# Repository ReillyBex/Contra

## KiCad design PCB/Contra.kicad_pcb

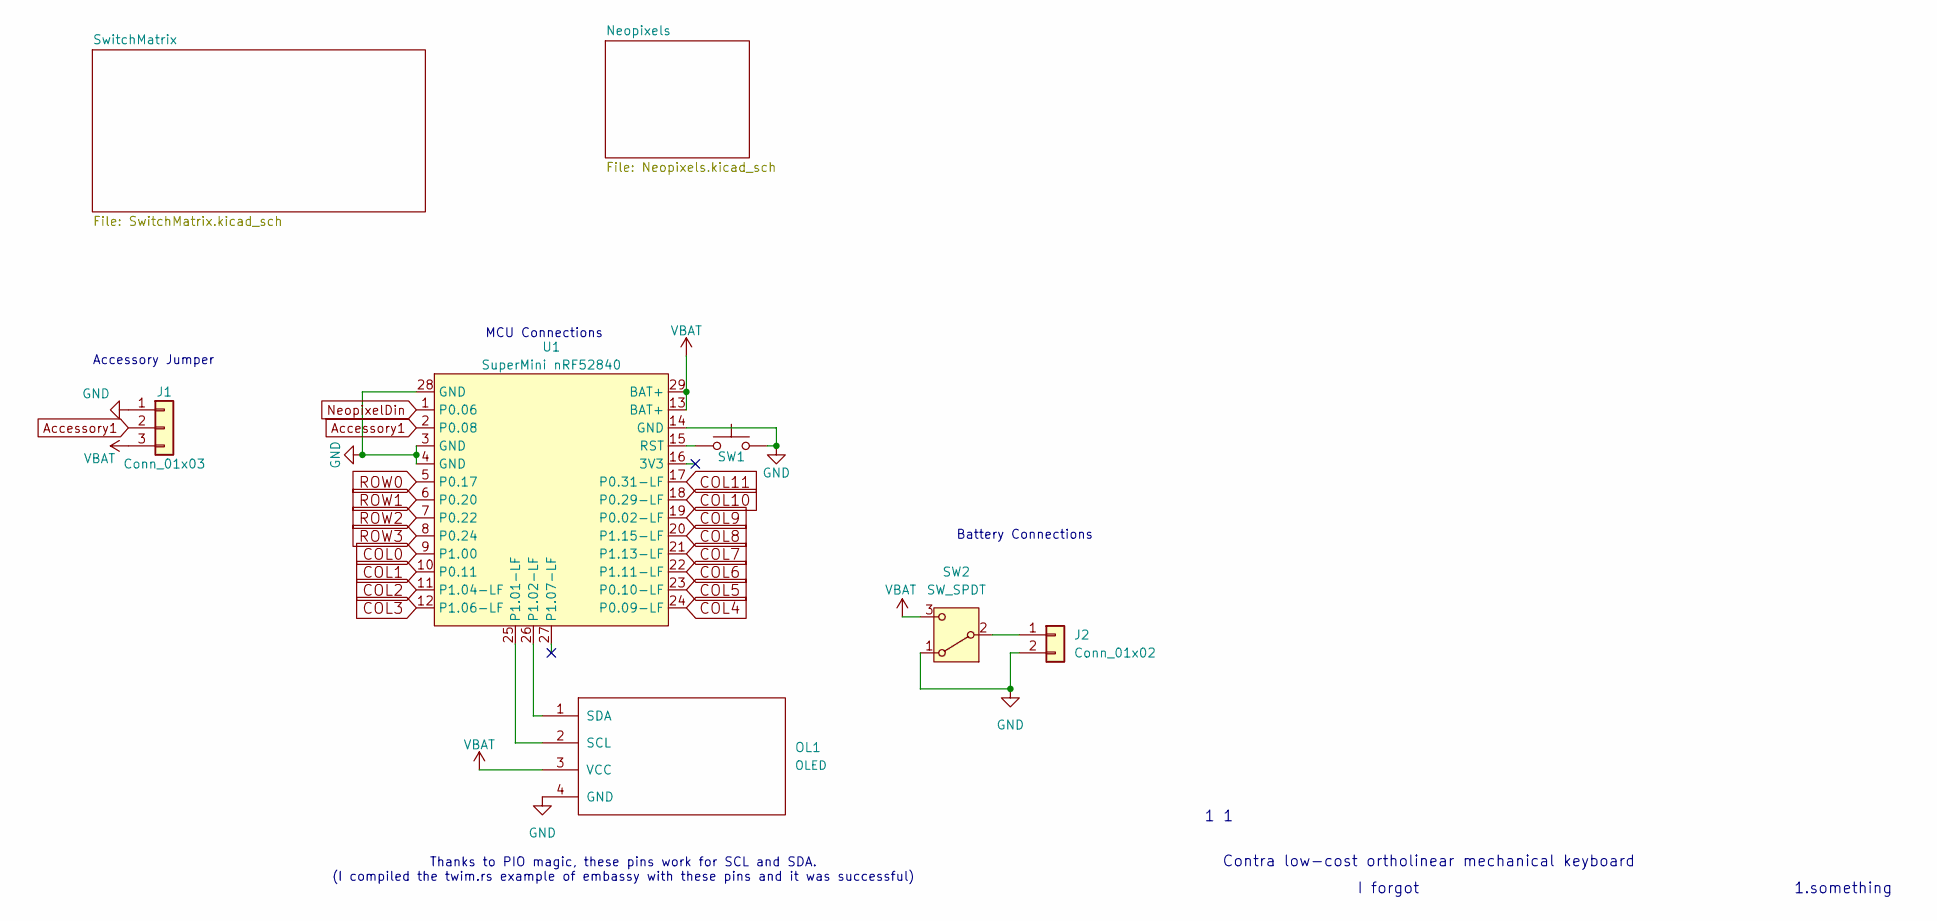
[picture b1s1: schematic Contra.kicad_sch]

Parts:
J1: Conn_01x03; PinHeader_1x03_P2.54mm_Horizontal
J2: Conn_01x02; JST_XH_S2B-XH-A_1x02_P2.50mm_Horizontal
OL1: OLED
SW1: SW_PUSH; SW_PUSH_1P1T_6x3.5mm_H5.0_APEM_MJTP1250
SW2: SW_SPDT; SW_Slide_SPDT_Angled_CK_OS102011MA1Q
U1: SuperMini nRF52840; SuperMini NRF52840

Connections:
Accessory1: J1.2, U1.2 (P0.08)
COL0: U1.9 (P1.00); also elsewhere on the board
COL1: U1.10 (P0.11); also elsewhere on the board
COL2: U1.11 (P1.04-LF); also elsewhere on the board
COL3: U1.12 (P1.06-LF); also elsewhere on the board
COL4: U1.24 (P0.09-LF); also elsewhere on the board
COL5: U1.23 (P0.10-LF); also elsewhere on the board
COL6: U1.22 (P1.11-LF); also elsewhere on the board
COL7: U1.21 (P1.13-LF); also elsewhere on the board
COL8: U1.20 (P1.15-LF); also elsewhere on the board
COL9: U1.19 (P0.02-LF); also elsewhere on the board
COL10: U1.18 (P0.29-LF); also elsewhere on the board
COL11: U1.17 (P0.31-LF); also elsewhere on the board
GND: J1.1, J2.2, OL1.4 (GND), SW1.2, SW2.1 (A), U1.3 (GND), U1.4 (GND), U1.14 (GND), U1.28 (GND); also elsewhere on the board
NeopixelDin: U1.1 (P0.06); also elsewhere on the board
unnamed: J2.1, SW2.2 (B)
unnamed: OL1.2 (SCL), U1.25 (P1.01-LF)
unnamed: OL1.1 (SDA), U1.26 (P1.02-LF)
unnamed: SW1.1, U1.15 (RST)
ROW0: U1.5 (P0.17); also elsewhere on the board
ROW1: U1.6 (P0.20); also elsewhere on the board
ROW2: U1.7 (P0.22); also elsewhere on the board
ROW3: U1.8 (P0.24); also elsewhere on the board
VBAT: J1.3, OL1.3 (VCC), SW2.3 (C), U1.13 (BAT+), U1.29 (BAT+); also elsewhere on the board

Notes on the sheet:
1.something
Battery Connections
1 1
I forgot
MCU Connections
Thanks to PIO magic, these pins work for SCL and SDA. (I compiled the twim.rs example of embassy with these pins and it was successful)
Contra low-cost ortholinear mechanical keyboard
Accessory Jumper

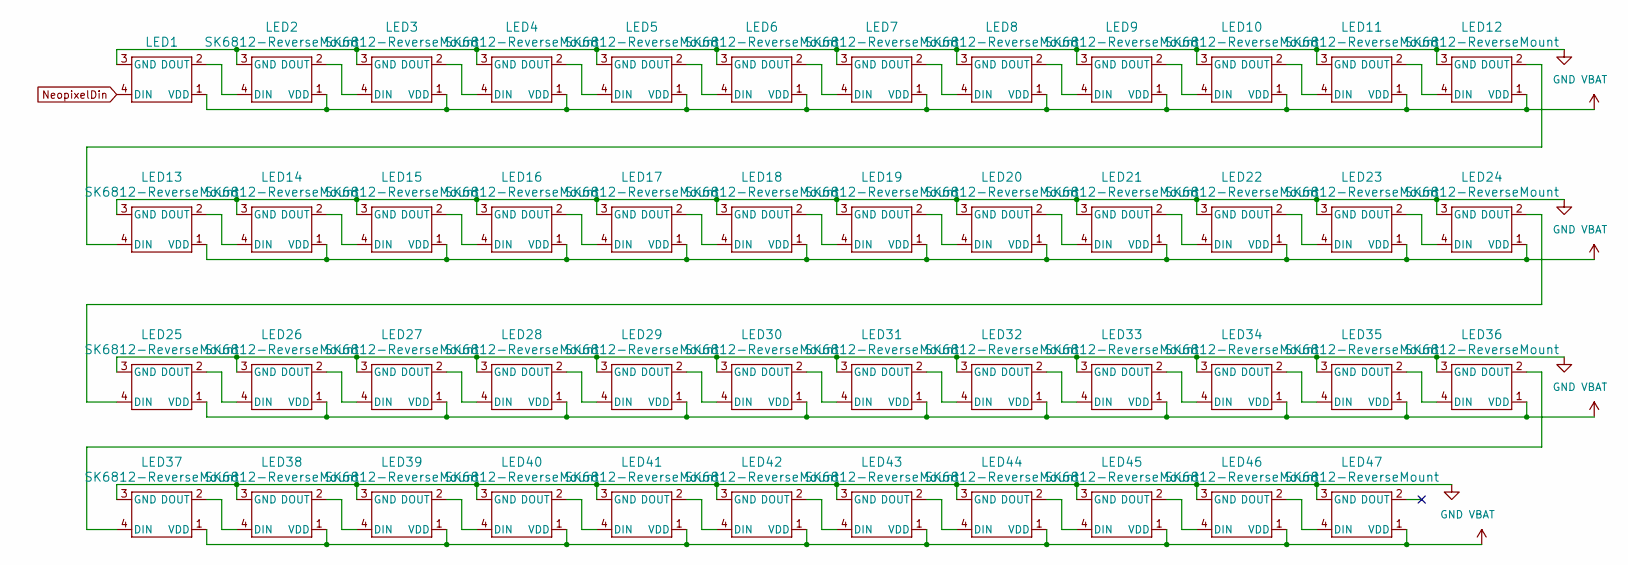
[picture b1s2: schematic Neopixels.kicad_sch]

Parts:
LED1, LED2, LED3, LED4, LED5, LED6, LED7, LED8, LED9, LED10, LED11, LED12, LED13, LED14, LED15, LED16, LED17, LED18, LED19, LED20, LED21, LED22, LED23, LED24, LED25, LED26, LED27, LED28, LED29, LED30, LED31, LED32, LED33, LED34, LED35, LED36, LED37, LED38, LED39, LED40, LED41, LED42, LED43, LED44, LED45, LED46, LED47: SK6812-ReverseMount; YS-SK6812MINI-E

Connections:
GND: LED1.3 (GND), LED2.3 (GND), LED3.3 (GND), LED4.3 (GND), LED5.3 (GND), LED6.3 (GND), LED7.3 (GND), LED8.3 (GND), LED9.3 (GND), LED10.3 (GND), LED11.3 (GND), LED12.3 (GND), LED13.3 (GND), LED14.3 (GND), LED15.3 (GND), LED16.3 (GND), LED17.3 (GND), LED18.3 (GND), LED19.3 (GND), LED20.3 (GND), LED21.3 (GND), LED22.3 (GND), LED23.3 (GND), LED24.3 (GND), LED25.3 (GND), LED26.3 (GND), LED27.3 (GND), LED28.3 (GND), LED29.3 (GND), LED30.3 (GND), LED31.3 (GND), LED32.3 (GND), LED33.3 (GND), LED34.3 (GND), LED35.3 (GND), LED36.3 (GND), LED37.3 (GND), LED38.3 (GND), LED39.3 (GND), LED40.3 (GND), LED41.3 (GND), LED42.3 (GND), LED43.3 (GND), LED44.3 (GND), LED45.3 (GND), LED46.3 (GND), LED47.3 (GND); also elsewhere on the board
NeopixelDin: LED1.4 (DIN); also elsewhere on the board
unnamed: LED1.2 (DOUT), LED2.4 (DIN)
unnamed: LED2.2 (DOUT), LED3.4 (DIN)
unnamed: LED3.2 (DOUT), LED4.4 (DIN)
unnamed: LED4.2 (DOUT), LED5.4 (DIN)
unnamed: LED5.2 (DOUT), LED6.4 (DIN)
unnamed: LED6.2 (DOUT), LED7.4 (DIN)
unnamed: LED7.2 (DOUT), LED8.4 (DIN)
unnamed: LED8.2 (DOUT), LED9.4 (DIN)
unnamed: LED9.2 (DOUT), LED10.4 (DIN)
unnamed: LED10.2 (DOUT), LED11.4 (DIN)
unnamed: LED11.2 (DOUT), LED12.4 (DIN)
unnamed: LED12.2 (DOUT), LED13.4 (DIN)
unnamed: LED13.2 (DOUT), LED14.4 (DIN)
unnamed: LED14.2 (DOUT), LED15.4 (DIN)
unnamed: LED15.2 (DOUT), LED16.4 (DIN)
unnamed: LED16.2 (DOUT), LED17.4 (DIN)
unnamed: LED17.2 (DOUT), LED18.4 (DIN)
unnamed: LED18.2 (DOUT), LED19.4 (DIN)
unnamed: LED19.2 (DOUT), LED20.4 (DIN)
unnamed: LED20.2 (DOUT), LED21.4 (DIN)
unnamed: LED21.2 (DOUT), LED22.4 (DIN)
unnamed: LED22.2 (DOUT), LED23.4 (DIN)
unnamed: LED23.2 (DOUT), LED24.4 (DIN)
unnamed: LED24.2 (DOUT), LED25.4 (DIN)
unnamed: LED25.2 (DOUT), LED26.4 (DIN)
unnamed: LED26.2 (DOUT), LED27.4 (DIN)
unnamed: LED27.2 (DOUT), LED28.4 (DIN)
unnamed: LED28.2 (DOUT), LED29.4 (DIN)
unnamed: LED29.2 (DOUT), LED30.4 (DIN)
unnamed: LED30.2 (DOUT), LED31.4 (DIN)
unnamed: LED31.2 (DOUT), LED32.4 (DIN)
unnamed: LED32.2 (DOUT), LED33.4 (DIN)
unnamed: LED33.2 (DOUT), LED34.4 (DIN)
unnamed: LED34.2 (DOUT), LED35.4 (DIN)
unnamed: LED35.2 (DOUT), LED36.4 (DIN)
unnamed: LED36.2 (DOUT), LED37.4 (DIN)
unnamed: LED37.2 (DOUT), LED38.4 (DIN)
unnamed: LED38.2 (DOUT), LED39.4 (DIN)
unnamed: LED39.2 (DOUT), LED40.4 (DIN)
unnamed: LED40.2 (DOUT), LED41.4 (DIN)
unnamed: LED41.2 (DOUT), LED42.4 (DIN)
unnamed: LED42.2 (DOUT), LED43.4 (DIN)
unnamed: LED43.2 (DOUT), LED44.4 (DIN)
unnamed: LED44.2 (DOUT), LED45.4 (DIN)
unnamed: LED45.2 (DOUT), LED46.4 (DIN)
unnamed: LED46.2 (DOUT), LED47.4 (DIN)
VBAT: LED1.1 (VDD), LED2.1 (VDD), LED3.1 (VDD), LED4.1 (VDD), LED5.1 (VDD), LED6.1 (VDD), LED7.1 (VDD), LED8.1 (VDD), LED9.1 (VDD), LED10.1 (VDD), LED11.1 (VDD), LED12.1 (VDD), LED13.1 (VDD), LED14.1 (VDD), LED15.1 (VDD), LED16.1 (VDD), LED17.1 (VDD), LED18.1 (VDD), LED19.1 (VDD), LED20.1 (VDD), LED21.1 (VDD), LED22.1 (VDD), LED23.1 (VDD), LED24.1 (VDD), LED25.1 (VDD), LED26.1 (VDD), LED27.1 (VDD), LED28.1 (VDD), LED29.1 (VDD), LED30.1 (VDD), LED31.1 (VDD), LED32.1 (VDD), LED33.1 (VDD), LED34.1 (VDD), LED35.1 (VDD), LED36.1 (VDD), LED37.1 (VDD), LED38.1 (VDD), LED39.1 (VDD), LED40.1 (VDD), LED41.1 (VDD), LED42.1 (VDD), LED43.1 (VDD), LED44.1 (VDD), LED45.1 (VDD), LED46.1 (VDD), LED47.1 (VDD); also elsewhere on the board

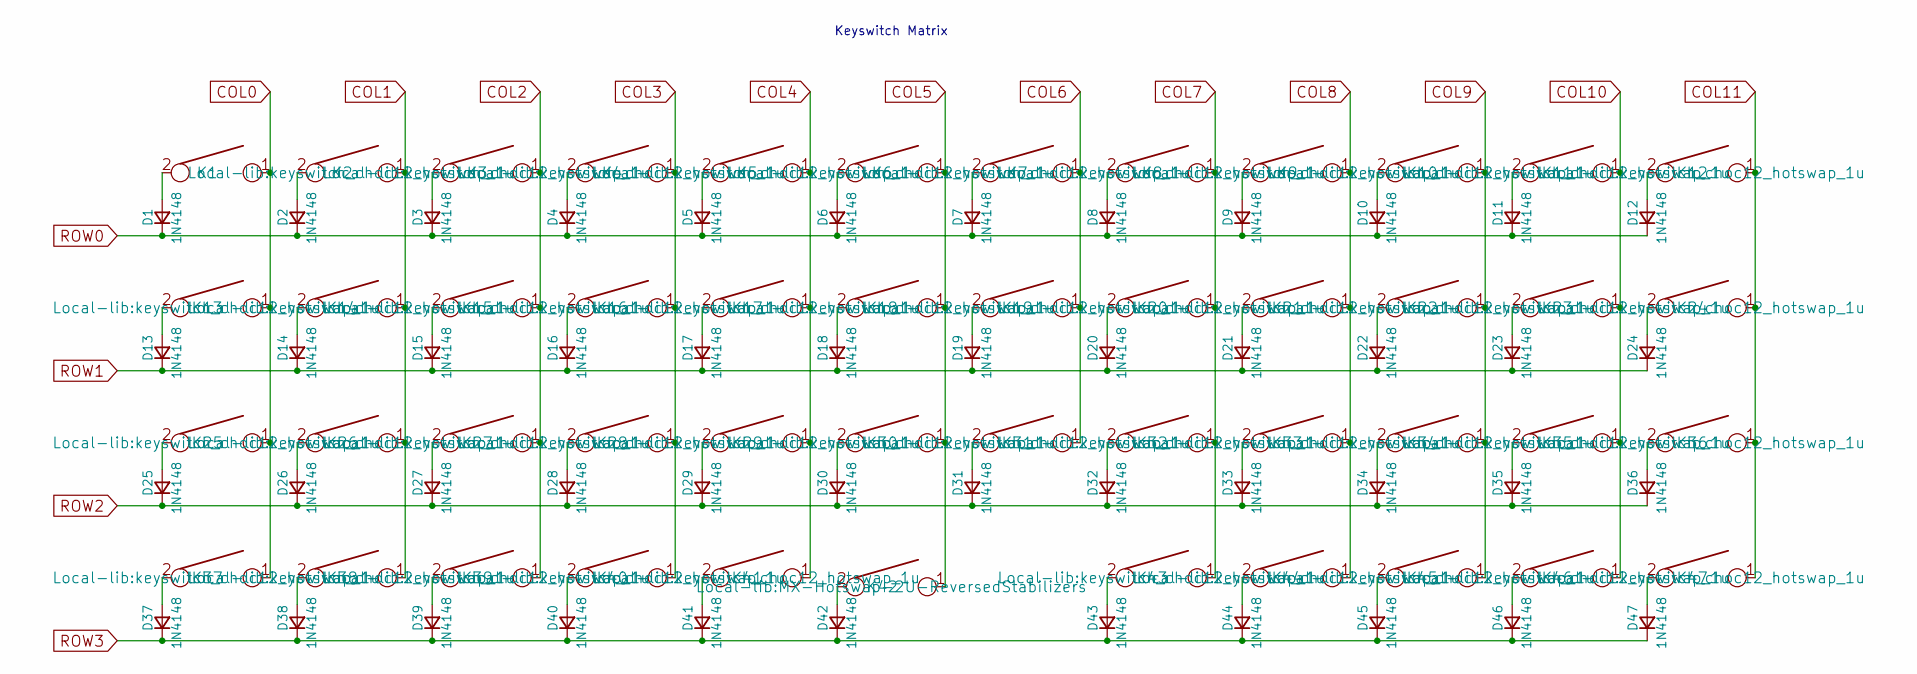
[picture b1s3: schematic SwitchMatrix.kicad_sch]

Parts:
D1, D2, D3, D4, D5, D6, D7, D8, D9, D10, D11, D12, D13, D14, D15, D16, D17, D18, D19, D20, D21, D22, D23, D24, D25, D26, D27, D28, D29, D30, D31, D32, D33, D34, D35, D36, D37, D38, D39, D40, D41, D42, D43, D44, D45, D46, D47: 1N4148; D_DO-35_SOD27_P7.62mm_Horizontal
K1, K2, K3, K4, K5, K6, K7, K8, K9, K10, K11, K12, K13, K14, K15, K16, K17, K18, K19, K20, K21, K22, K23, K24, K25, K26, K27, K28, K29, K30, K31, K32, K33, K34, K35, K36, K37, K38, K39, K40, K41, K43, K44, K45, K46, K47: KEYSW; keyswitch_choc12_hotswap_1u
K42: KEYSW; MX-Hotswap-2U-ReversedStabilizers

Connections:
COL0: K1.1, K13.1, K25.1, K37.1; also elsewhere on the board
COL1: K2.1, K14.1, K26.1, K38.1; also elsewhere on the board
COL2: K3.1, K15.1, K27.1, K39.1; also elsewhere on the board
COL3: K4.1, K16.1, K28.1, K40.1; also elsewhere on the board
COL4: K5.1, K17.1, K29.1, K41.1; also elsewhere on the board
COL5: K6.1, K18.1, K30.1, K42.1; also elsewhere on the board
COL6: K7.1, K19.1, K31.1; also elsewhere on the board
COL7: K8.1, K20.1, K32.1, K43.1; also elsewhere on the board
COL8: K9.1, K21.1, K33.1, K44.1; also elsewhere on the board
COL9: K10.1, K22.1, K34.1, K45.1; also elsewhere on the board
COL10: K11.1, K23.1, K35.1, K46.1; also elsewhere on the board
COL11: K12.1, K24.1, K36.1, K47.1; also elsewhere on the board
unnamed: D1.2 (A), K1.2
unnamed: D2.2 (A), K2.2
unnamed: D3.2 (A), K3.2
unnamed: D4.2 (A), K4.2
unnamed: D5.2 (A), K5.2
unnamed: D6.2 (A), K6.2
unnamed: D7.2 (A), K7.2
unnamed: D8.2 (A), K8.2
unnamed: D9.2 (A), K9.2
unnamed: D10.2 (A), K10.2
unnamed: D11.2 (A), K11.2
unnamed: D12.2 (A), K12.2
unnamed: D13.2 (A), K13.2
unnamed: D14.2 (A), K14.2
unnamed: D15.2 (A), K15.2
unnamed: D16.2 (A), K16.2
unnamed: D17.2 (A), K17.2
unnamed: D18.2 (A), K18.2
unnamed: D19.2 (A), K19.2
unnamed: D20.2 (A), K20.2
unnamed: D21.2 (A), K21.2
unnamed: D22.2 (A), K22.2
unnamed: D23.2 (A), K23.2
unnamed: D24.2 (A), K24.2
unnamed: D25.2 (A), K25.2
unnamed: D26.2 (A), K26.2
unnamed: D27.2 (A), K27.2
unnamed: D28.2 (A), K28.2
unnamed: D29.2 (A), K29.2
unnamed: D30.2 (A), K30.2
unnamed: D31.2 (A), K31.2
unnamed: D32.2 (A), K32.2
unnamed: D33.2 (A), K33.2
unnamed: D34.2 (A), K34.2
unnamed: D35.2 (A), K35.2
unnamed: D36.2 (A), K36.2
unnamed: D37.2 (A), K37.2
unnamed: D38.2 (A), K38.2
unnamed: D39.2 (A), K39.2
unnamed: D40.2 (A), K40.2
unnamed: D41.2 (A), K41.2
unnamed: D42.2 (A), K42.2
unnamed: D43.2 (A), K43.2
unnamed: D44.2 (A), K44.2
unnamed: D45.2 (A), K45.2
unnamed: D46.2 (A), K46.2
unnamed: D47.2 (A), K47.2
ROW0: D1.1 (K), D2.1 (K), D3.1 (K), D4.1 (K), D5.1 (K), D6.1 (K), D7.1 (K), D8.1 (K), D9.1 (K), D10.1 (K), D11.1 (K), D12.1 (K); also elsewhere on the board
ROW1: D13.1 (K), D14.1 (K), D15.1 (K), D16.1 (K), D17.1 (K), D18.1 (K), D19.1 (K), D20.1 (K), D21.1 (K), D22.1 (K), D23.1 (K), D24.1 (K); also elsewhere on the board
ROW2: D25.1 (K), D26.1 (K), D27.1 (K), D28.1 (K), D29.1 (K), D30.1 (K), D31.1 (K), D32.1 (K), D33.1 (K), D34.1 (K), D35.1 (K), D36.1 (K); also elsewhere on the board
ROW3: D37.1 (K), D38.1 (K), D39.1 (K), D40.1 (K), D41.1 (K), D42.1 (K), D43.1 (K), D44.1 (K), D45.1 (K), D46.1 (K), D47.1 (K); also elsewhere on the board

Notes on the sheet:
Keyswitch Matrix

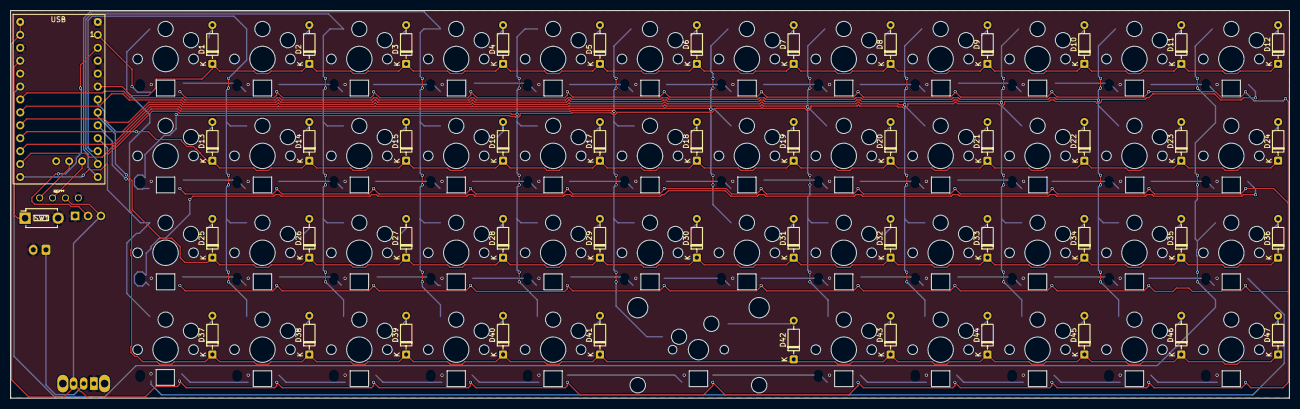
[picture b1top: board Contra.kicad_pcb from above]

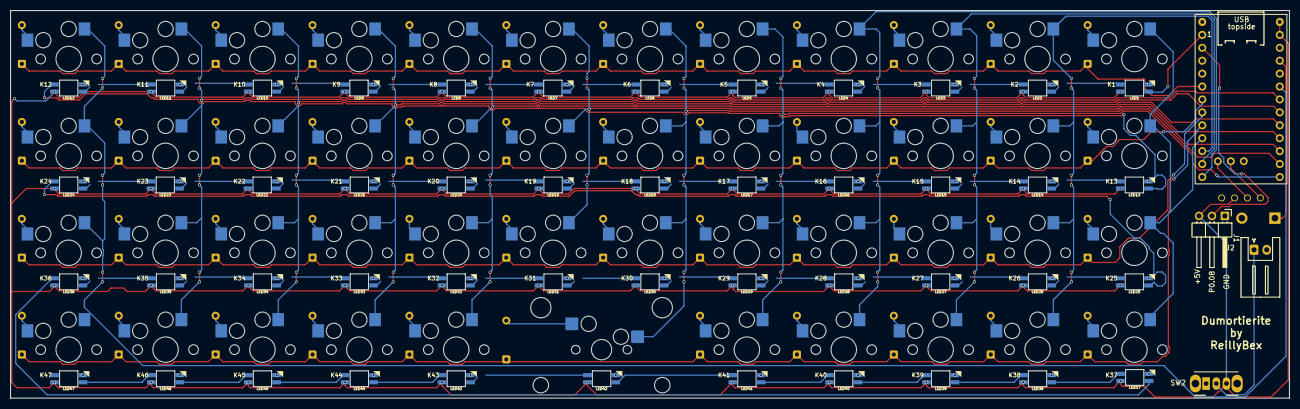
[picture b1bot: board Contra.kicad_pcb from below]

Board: 2 copper layers, 251.5 x 76.2 mm, 147 parts (98 on the bottom side), 117 nets.
